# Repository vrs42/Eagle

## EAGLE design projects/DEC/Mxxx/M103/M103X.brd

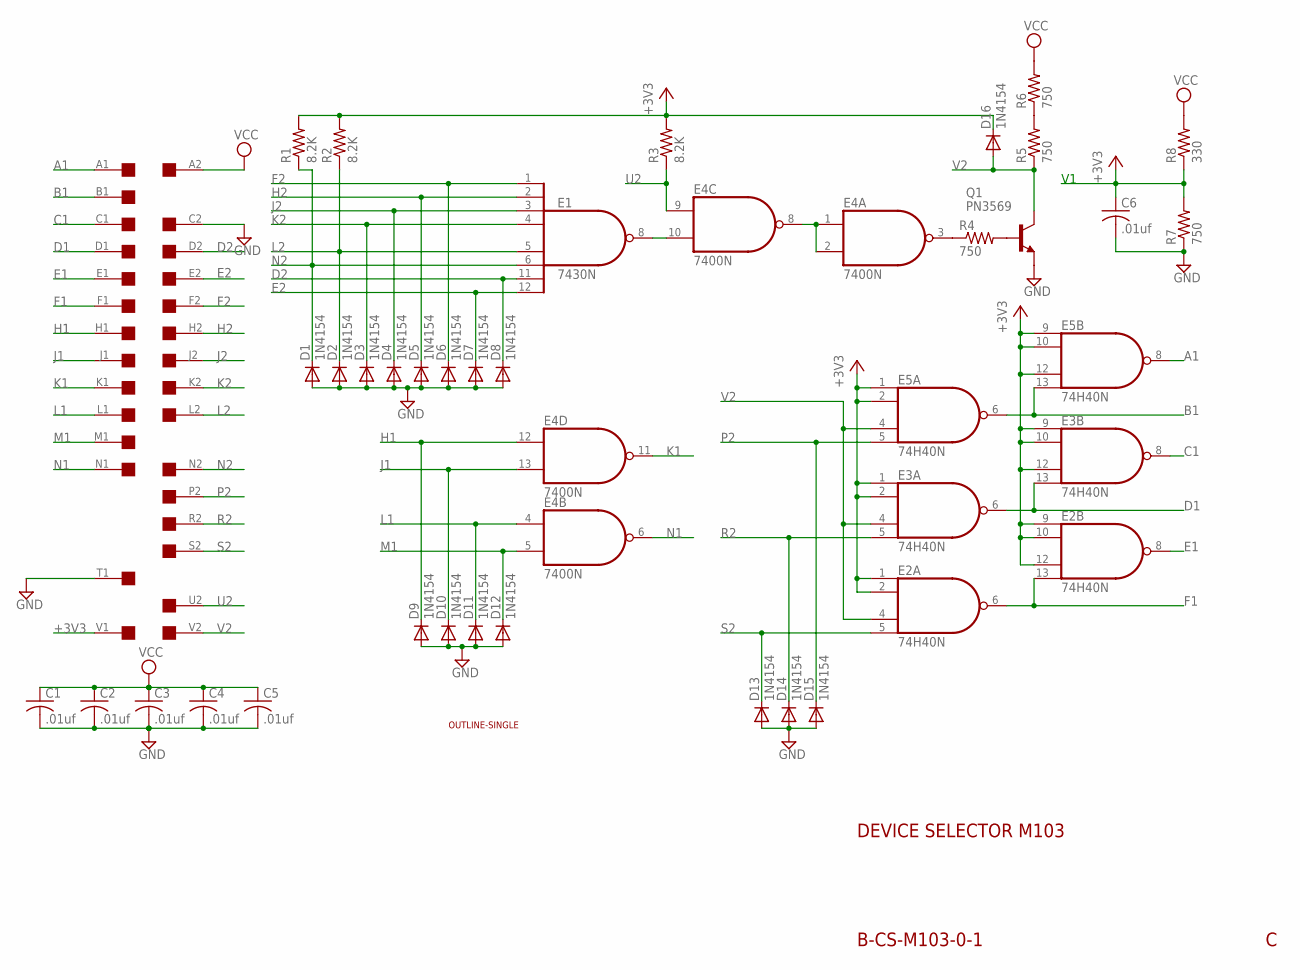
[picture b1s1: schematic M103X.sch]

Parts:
C1, C2, C3, C4, C5, C6: .01uf; C050-025X075
D1, D2, D3, D4, D5, D6, D7, D8, D9, D10, D11, D12, D13, D14, D15, D16: 1N4154; DO35-10
E1: 7430N; DIL14
E2, E3, E5: 74H40N; DIL14
E4: 7400N; DIL14
Q1: PN3569; TO39
R1, R2, R3: 8.2K; 0207/10
R4, R5, R6, R7: 750; 0207/10
R8: 330; 0207/10
U$8: SINGLE; EDGE-CON2
U$9: OUTLINE-SINGLE; SINGLE

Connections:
+3V3: C6.1, D16.C, E2.1 (I0), E2.2 (I1), E2.9 (I0), E2.10 (I1), E2.12 (I2), E3.1 (I0), E3.2 (I1), E3.9 (I0), E3.10 (I1), E3.12 (I2), E5.1 (I0), E5.2 (I1), E5.9 (I0), E5.10 (I1), E5.12 (I2), R1.2, R2.2, R3.2, R7.2, R8.1, U$8.V1
A1: E5.8 (O), U$8.A1
B1: E5.6 (O), E5.13 (I3), U$8.B1
C1: E3.8 (O), U$8.C1
D1: E3.6 (O), E3.13 (I3), U$8.D1
D2: D8.C, E1.11 (I6), U$8.D2
E1: E2.8 (O), U$8.E1
E2: D7.C, E1.12 (I7), U$8.E2
F1: E2.6 (O), E2.13 (I3), U$8.F1
F2: D6.C, E1.1 (I0), U$8.F2
GND: C1.2, C2.2, C3.2, C4.2, C5.2, C6.2, D1.A, D2.A, D3.A, D4.A, D5.A, D6.A, D7.A, D8.A, D9.A, D10.A, D11.A, D12.A, D13.A, D14.A, D15.A, E1.7 (GND), E2.7 (GND), E3.7 (GND), E4.7 (GND), E5.7 (GND), Q1.1 (E), R7.1, U$8.C2, U$8.T1
H1: D9.C, E4.12 (I0), U$8.H1
H2: D5.C, E1.2 (I1), U$8.H2
J1: D10.C, E4.13 (I1), U$8.J1
J2: D4.C, E1.3 (I2), U$8.J2
K1: E4.11 (O), U$8.K1
K2: D3.C, E1.4 (I3), U$8.K2
L1: D11.C, E4.4 (I0), U$8.L1
L2: D2.C, E1.5 (I4), R2.1, U$8.L2
M1: D12.C, E4.5 (I1), U$8.M1
N1: E4.6 (O), U$8.N1
N2: D1.C, E1.6 (I5), R1.1, U$8.N2
unnamed: E4.3 (O), R4.1
unnamed: Q1.2 (B), R4.2
unnamed: R5.2, R6.1
unnamed: E1.8 (O), E4.10 (I1)
unnamed: E4.1 (I0), E4.2 (I1), E4.8 (O)
P2: D15.C, E5.5 (I3), U$8.P2
R2: D14.C, E3.5 (I3), U$8.R2
S2: D13.C, E2.5 (I3), U$8.S2
U2: E4.9 (I0), R3.1, U$8.U2
V2: D16.A, E2.4 (I2), E3.4 (I2), E5.4 (I2), Q1.3 (C), R5.1, U$8.V2
VCC: C1.1, C2.1, C3.1, C4.1, C5.1, E1.14 (VCC), E2.14 (VCC), E3.14 (VCC), E4.14 (VCC), E5.14 (VCC), R6.2, R8.2, U$8.A2

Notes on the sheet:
DEVICE SELECTOR M103
B-CS-M103-0-1

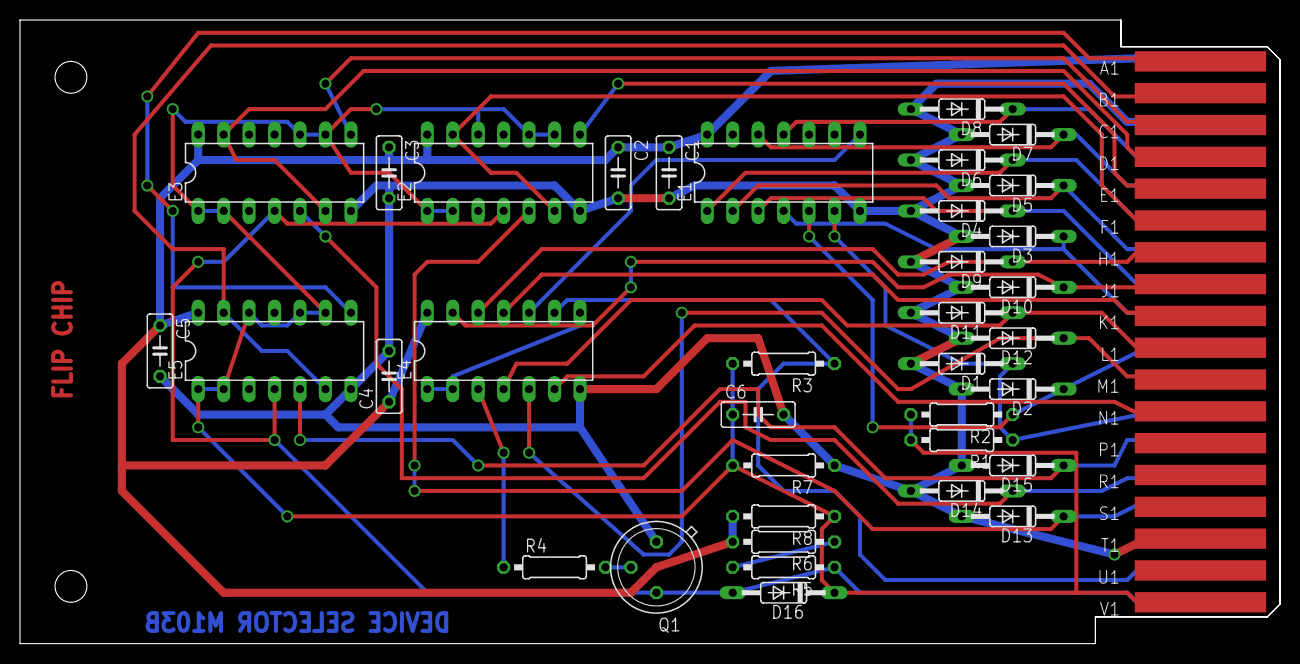
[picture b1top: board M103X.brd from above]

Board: 2 copper layers, 125.7 x 62.2 mm, 38 parts (0 on the bottom side), 33 nets.

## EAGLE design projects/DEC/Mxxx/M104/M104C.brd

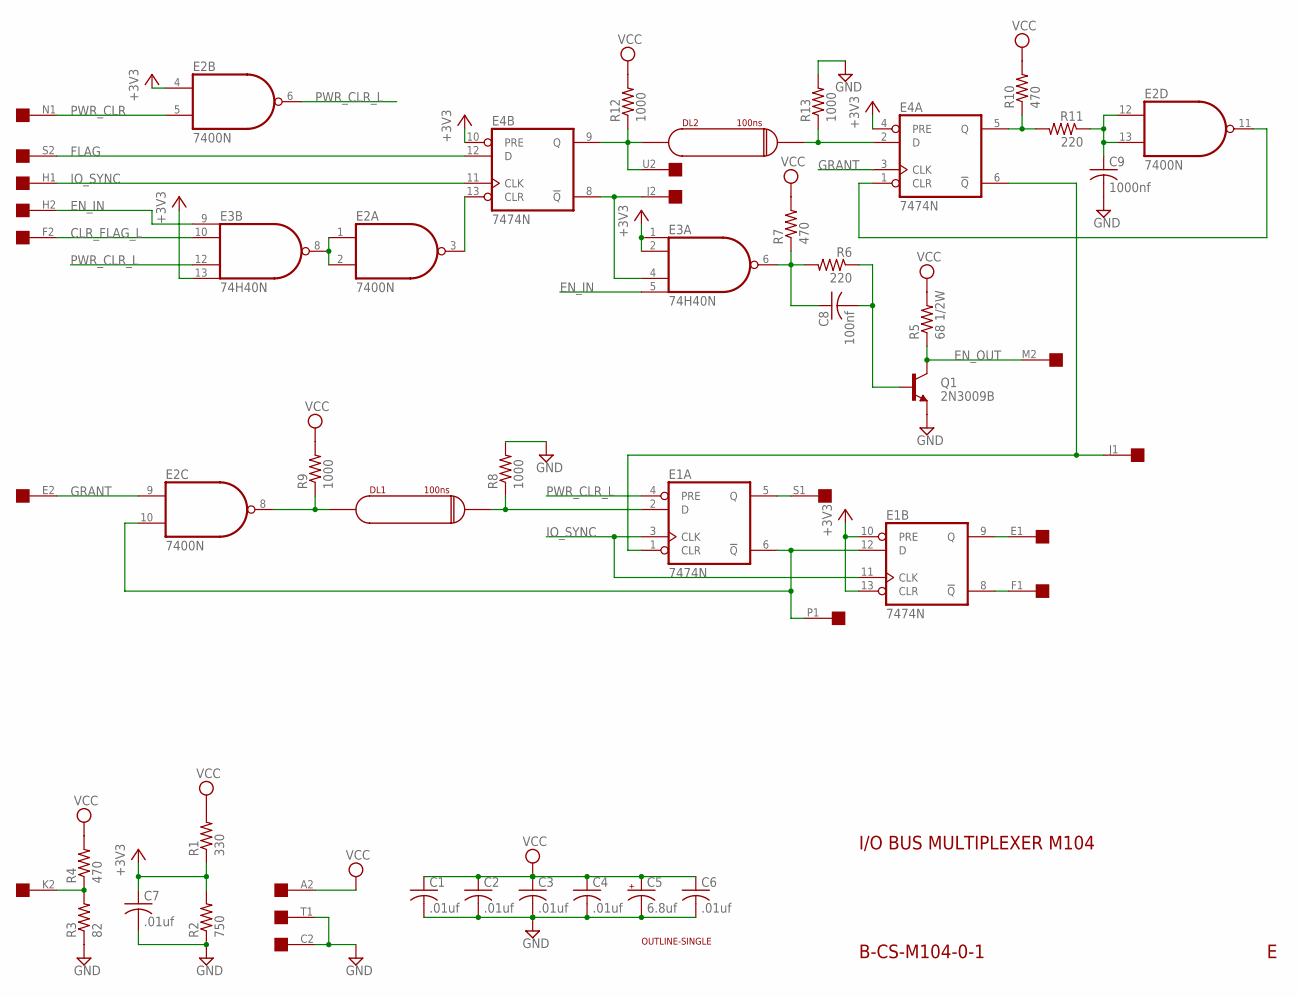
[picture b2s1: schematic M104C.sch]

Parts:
C1, C2, C3, C4, C6, C7: .01uf; C050-025X075
C5: 6.8uf; E15-5
C8: 100nf; C050-025X075
C9: 1000nf; C050-025X075
DL1, DL2: 100ns; RCL-L-XX-22
E1, E4: 7474N; DIL14
E2: 7400N; DIL14
E3: 74H40N; DIL14
Q1: 2N3009B; TO39
R1: 330; 0207/10
R2: 750; 0207/10
R3: 82; 0207/10
R4, R7, R10: 470; 0207/10
R5: 68 1/2W; 0411/15
R6, R11: 220; 0207/10
R8, R9, R12, R13: 1000; 0207/10
U$8: SINGLE; EDGE-CON2
U$9: OUTLINE-SINGLE; SINGLE

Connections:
+3V3: C7.1, E1.10 (PRE), E1.13 (CLR), E2.4 (I0), E3.1 (I0), E3.2 (I1), E3.13 (I3), E4.4 (PRE), E4.10 (PRE), R1.1, R2.2
CLR_FLAG_L: E3.10 (I1), U$8.F2
EN_IN: E3.5 (I3), E3.9 (I0), U$8.H2
EN_OUT: Q1.3 (C), R5.1, U$8.M2
FLAG: E4.12 (D), U$8.S2
GND: C1.2, C2.2, C3.2, C4.2, C5.-, C6.2, C7.2, C9.2, DL1.GND@1 (GND), DL1.GND@2 (GND), DL2.GND@1 (GND), DL2.GND@2 (GND), E1.7 (GND), E2.7 (GND), E3.7 (GND), E4.7 (GND), Q1.1 (E), R2.1, R3.1, R8.2, R13.2, U$8.C2, U$8.T1
GRANT: E2.9 (I0), E4.3 (CLK), U$8.E2
IO_SYNC: E1.3 (CLK), E1.11 (CLK), E4.11 (CLK), U$8.H1
K2: R3.2, R4.1, U$8.K2
unnamed: E1.1 (CLR), E4.6 (!Q), U$8.J1
unnamed: DL2.IN, E4.9 (Q), R12.1, U$8.U2
unnamed: E3.4 (I2), E4.8 (!Q), U$8.J2
unnamed: DL2.OUT, E4.2 (D), R13.1
unnamed: C8.1, E3.6 (O), R6.2, R7.1
unnamed: E2.1 (I0), E2.2 (I1), E3.8 (O)
unnamed: E2.3 (O), E4.13 (CLR)
unnamed: C9.1, E2.12 (I0), E2.13 (I1), R11.1
unnamed: E2.11 (O), E4.1 (CLR)
unnamed: DL1.IN, E2.8 (O), R9.1
unnamed: DL1.OUT, E1.2 (D), R8.1
unnamed: E1.6 (!Q), E1.12 (D), E2.10 (I1), U$8.P1
unnamed: E1.8 (!Q), U$8.F1
unnamed: E1.9 (Q), U$8.E1
unnamed: E1.5 (Q), U$8.S1
unnamed: E4.5 (Q), R10.1, R11.2
unnamed: C8.2, Q1.2 (B), R6.1
PWR_CLR: E2.5 (I1), U$8.N1
PWR_CLR_L: E1.4 (PRE), E2.6 (O), E3.12 (I2)
VCC: C1.1, C2.1, C3.1, C4.1, C5.+, C6.1, E1.14 (VCC), E2.14 (VCC), E3.14 (VCC), E4.14 (VCC), R1.2, R4.2, R5.2, R7.2, R9.2, R10.2, R12.2, U$8.A2

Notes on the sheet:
I/O BUS MULTIPLEXER M104
B-CS-M104-0-1

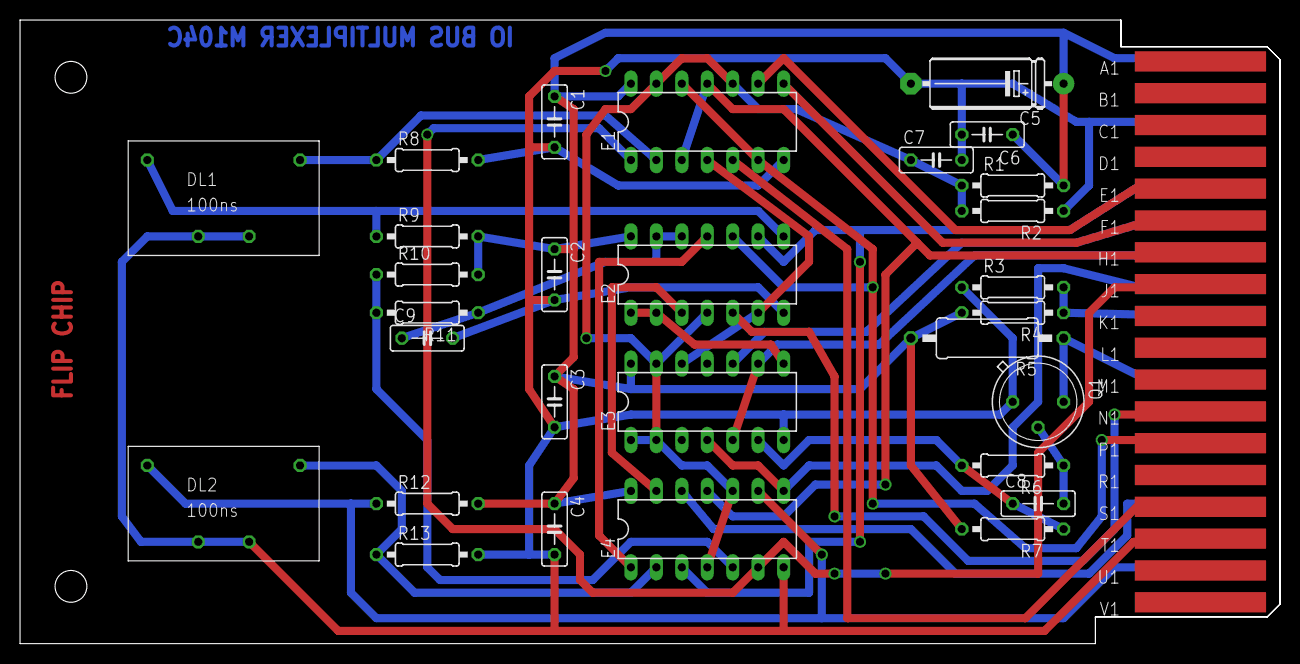
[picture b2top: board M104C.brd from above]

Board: 2 copper layers, 125.7 x 62.2 mm, 31 parts (0 on the bottom side), 29 nets.

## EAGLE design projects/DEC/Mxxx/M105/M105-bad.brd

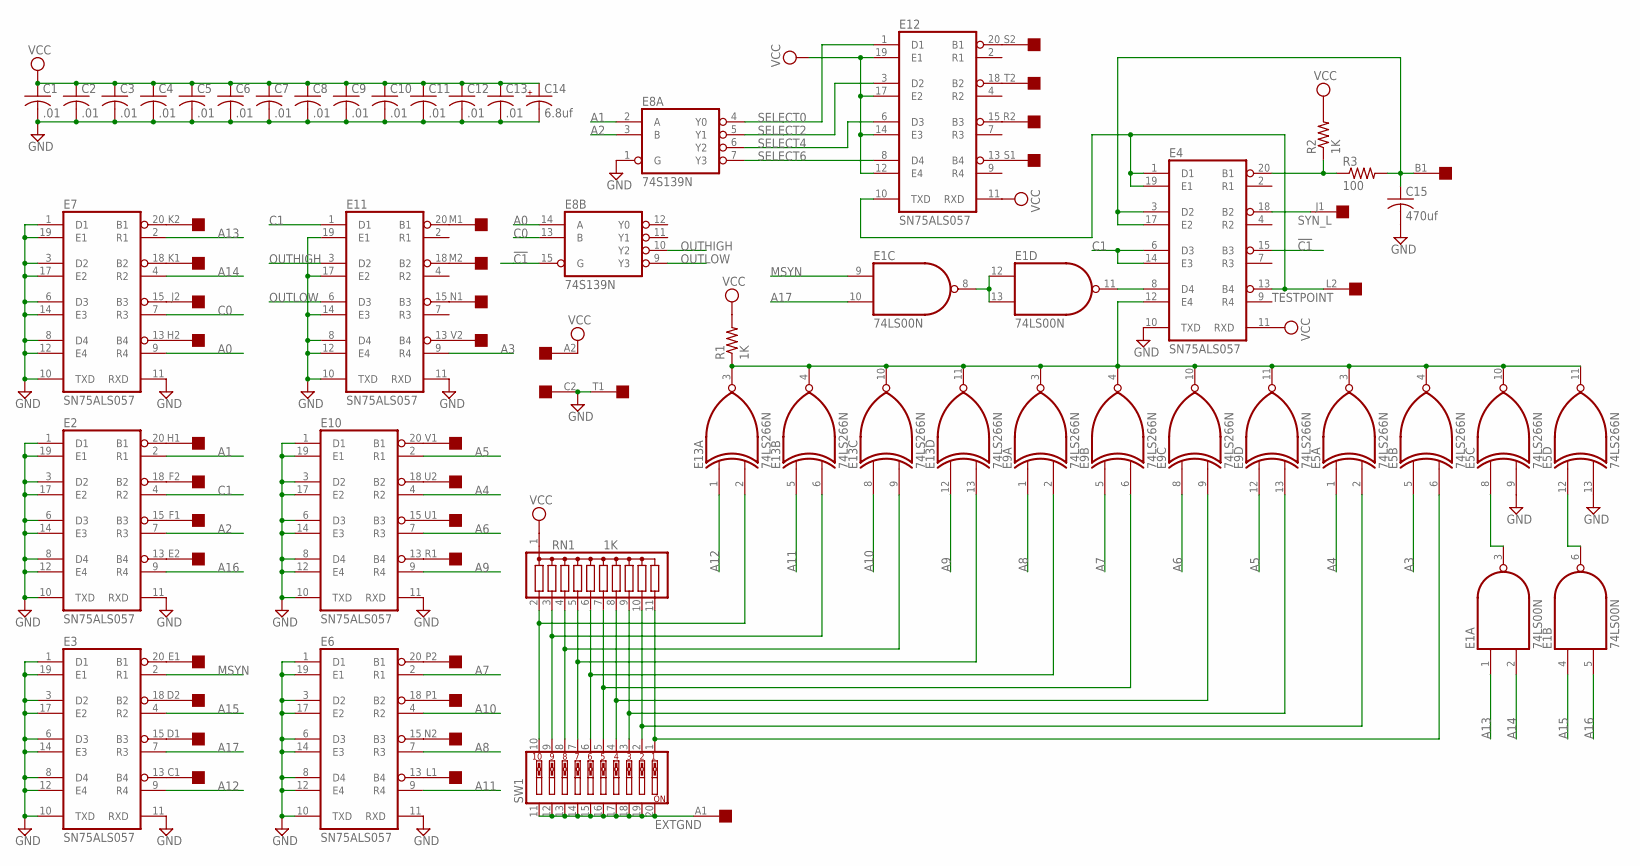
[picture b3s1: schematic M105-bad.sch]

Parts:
C1, C2, C3, C4, C5, C6, C7, C8, C9, C10, C11, C12, C13: .01; C050-025X075
C14: 6.8uf; E15-5
C15: 470uf; C050-025X075
E1: 74LS00N; DIL14
E2, E3, E4, E6, E7, E10, E11, E12: SN75ALS057; DIL20
E5, E9, E13: 74LS266N; DIL14
E8: 74S139N; DIL16
R1, R2: 1K; 0207/10
R3: 100; 0207/10
RN1: 1K; SIL11
SW1: SW_DIP-10; EDG-10
U$1: SINGLE; EDGE-CON2

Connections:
!C1: E4.15 (B3), E8.15 (G)
A0: E7.9 (R4), E8.14 (A)
A1: E2.2 (R1), E8.2 (A)
A2: E2.7 (R3), E8.3 (B)
A3: E5.5 (I0), E11.9 (R4)
A4: E5.1 (I0), E10.4 (R2)
A5: E9.12 (I0), E10.2 (R1)
A6: E9.8 (I0), E10.7 (R3)
A7: E6.2 (R1), E9.5 (I0)
A8: E6.7 (R3), E9.1 (I0)
A9: E10.9 (R4), E13.12 (I0)
A10: E6.4 (R2), E13.8 (I0)
A11: E6.9 (R4), E13.5 (I0)
A12: E3.9 (R4), E13.1 (I0)
A13: E1.1 (I0), E7.2 (R1)
A14: E1.2 (I1), E7.4 (R2)
A15: E1.4 (I0), E3.4 (R2)
A16: E1.5 (I1), E2.9 (R4)
A17: E1.10 (I1), E3.7 (R3)
C0: E7.7 (R3), E8.13 (B)
C1: E2.4 (R2), E4.6 (D3), E4.14 (E3), E11.1 (D1)
EXTGND: SW1.11, SW1.12, SW1.13, SW1.14, SW1.15, SW1.16, SW1.17, SW1.18, SW1.19, SW1.20, U$1.A1
GND: C1.2, C2.2, C3.2, C4.2, C5.2, C6.2, C7.2, C8.2, C9.2, C10.2, C11.2, C12.2, C13.2, C14.-, C15.2, E1.7 (GND), E2.1 (D1), E2.3 (D2), E2.6 (D3), E2.8 (D4), E2.10 (TXD), E2.11 (RXD), E2.12 (E4), E2.14 (E3), E2.16 (GND), E2.17 (E2), E2.19 (E1), E3.1 (D1), E3.3 (D2), E3.6 (D3), E3.8 (D4), E3.10 (TXD), E3.11 (RXD), E3.12 (E4), E3.14 (E3), E3.16 (GND), E3.17 (E2), E3.19 (E1), E4.10 (TXD), E4.16 (GND), E5.7 (GND), E5.9 (I1), E5.13 (I1), E6.1 (D1), E6.3 (D2), E6.6 (D3), E6.8 (D4), E6.10 (TXD), E6.11 (RXD), E6.12 (E4), E6.14 (E3), E6.16 (GND), E6.17 (E2), E6.19 (E1), E7.1 (D1), E7.3 (D2), E7.6 (D3), E7.8 (D4), E7.10 (TXD), E7.11 (RXD), E7.12 (E4), E7.14 (E3), E7.16 (GND), E7.17 (E2), E7.19 (E1), E8.1 (G), E8.8 (GND), E9.7 (GND), E10.1 (D1), E10.3 (D2), E10.6 (D3), E10.8 (D4), E10.10 (TXD), E10.11 (RXD), E10.12 (E4), E10.14 (E3), E10.16 (GND), E10.17 (E2), E10.19 (E1), E11.8 (D4), E11.10 (TXD), E11.11 (RXD), E11.12 (E4), E11.14 (E3), E11.16 (GND), E11.17 (E2), E11.19 (E1), E12.16 (GND), E13.7 (GND), U$1.C2, U$1.T1
MSYN: E1.9 (I0), E3.2 (R1)
unnamed: E3.18 (B2), U$1.D2
unnamed: E3.20 (B1), U$1.E1
unnamed: E3.15 (B3), U$1.D1
unnamed: E3.13 (B4), U$1.C1
unnamed: E2.18 (B2), U$1.F2
unnamed: E2.13 (B4), U$1.E2
unnamed: E2.20 (B1), U$1.H1
unnamed: E2.15 (B3), U$1.F1
unnamed: E7.20 (B1), U$1.K2
unnamed: E7.15 (B3), U$1.J2
unnamed: E7.13 (B4), U$1.H2
unnamed: E7.18 (B2), U$1.K1
unnamed: E6.15 (B3), U$1.N2
unnamed: E6.20 (B1), U$1.P2
unnamed: E6.13 (B4), U$1.L1
unnamed: E6.18 (B2), U$1.P1
unnamed: E10.18 (B2), U$1.U2
unnamed: E11.13 (B4), U$1.V2
unnamed: E10.13 (B4), U$1.R1
unnamed: E10.15 (B3), U$1.U1
unnamed: E10.20 (B1), U$1.V1
unnamed: E4.20 (B1), R2.1, R3.1
unnamed: E12.20 (B1), U$1.S2
unnamed: E12.18 (B2), U$1.T2
unnamed: E12.13 (B4), U$1.S1
unnamed: E12.15 (B3), U$1.R2
unnamed: E11.18 (B2), U$1.M2
unnamed: E11.15 (B3), U$1.N1
unnamed: E1.3 (O), E5.8 (I0)
unnamed: E1.6 (O), E5.12 (I0)
unnamed: E1.8 (O), E1.12 (I0), E1.13 (I1)
unnamed: E1.11 (O), E4.8 (D4)
unnamed: E5.6 (I1), RN1.11, SW1.1
unnamed: E5.2 (I1), RN1.10, SW1.2
unnamed: E9.13 (I1), RN1.9, SW1.3
unnamed: E9.9 (I1), RN1.8, SW1.4
unnamed: E9.6 (I1), RN1.7, SW1.5
unnamed: E9.2 (I1), RN1.6, SW1.6
unnamed: E13.13 (I1), RN1.5, SW1.7
unnamed: E13.9 (I1), RN1.4, SW1.8
unnamed: E13.6 (I1), RN1.3, SW1.9
unnamed: E13.2 (I1), RN1.2, SW1.10
unnamed: E4.12 (E4), E5.3 (O), E5.4 (O), E5.10 (O), E5.11 (O), E9.3 (O), E9.4 (O), E9.10 (O), E9.11 (O), E13.3 (O), E13.4 (O), E13.10 (O), E13.11 (O), R1.1
unnamed: C15.1, E4.3 (D2), E4.17 (E2), R3.2, U$1.B1
unnamed: E11.20 (B1), U$1.M1
OUTHIGH: E8.10 (Y2), E11.3 (D2)
OUTLOW: E8.9 (Y3), E11.6 (D3)
SELECT0: E8.4 (Y0), E12.1 (D1)
SELECT2: E8.5 (Y1), E12.3 (D2)
SELECT4: E8.6 (Y2), E12.6 (D3)
SELECT6: E8.7 (Y3), E12.8 (D4)
SYN_L: E4.18 (B2), U$1.J1
TESTPOINT: E4.1 (D1), E4.13 (B4), E4.19 (E1), E12.10 (TXD), U$1.L2
VCC: C1.1, C2.1, C3.1, C4.1, C5.1, C6.1, C7.1, C8.1, C9.1, C10.1, C11.1, C12.1, C13.1, C14.+, E1.14 (VCC), E2.5 (VCC), E3.5 (VCC), E4.5 (VCC), E4.11 (RXD), E5.14 (VCC), E6.5 (VCC), E7.5 (VCC), E8.16 (VCC), E9.14 (VCC), E10.5 (VCC), E11.5 (VCC), E12.5 (VCC), E12.11 (RXD), E12.12 (E4), E12.14 (E3), E12.17 (E2), E12.19 (E1), E13.14 (VCC), R1.2, R2.2, RN1.1, U$1.A2

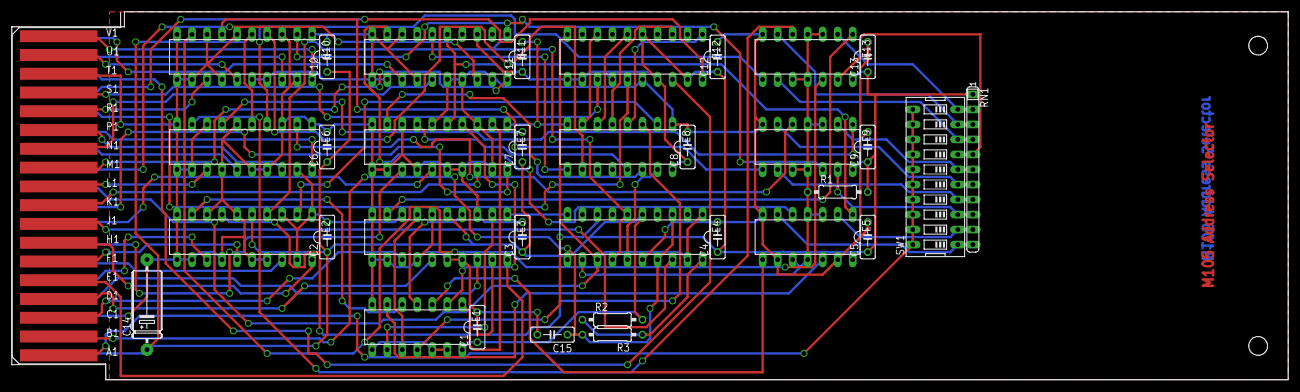
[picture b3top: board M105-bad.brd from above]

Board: 2 copper layers, 215.9 x 62.2 mm, 34 parts (0 on the bottom side), 78 nets.

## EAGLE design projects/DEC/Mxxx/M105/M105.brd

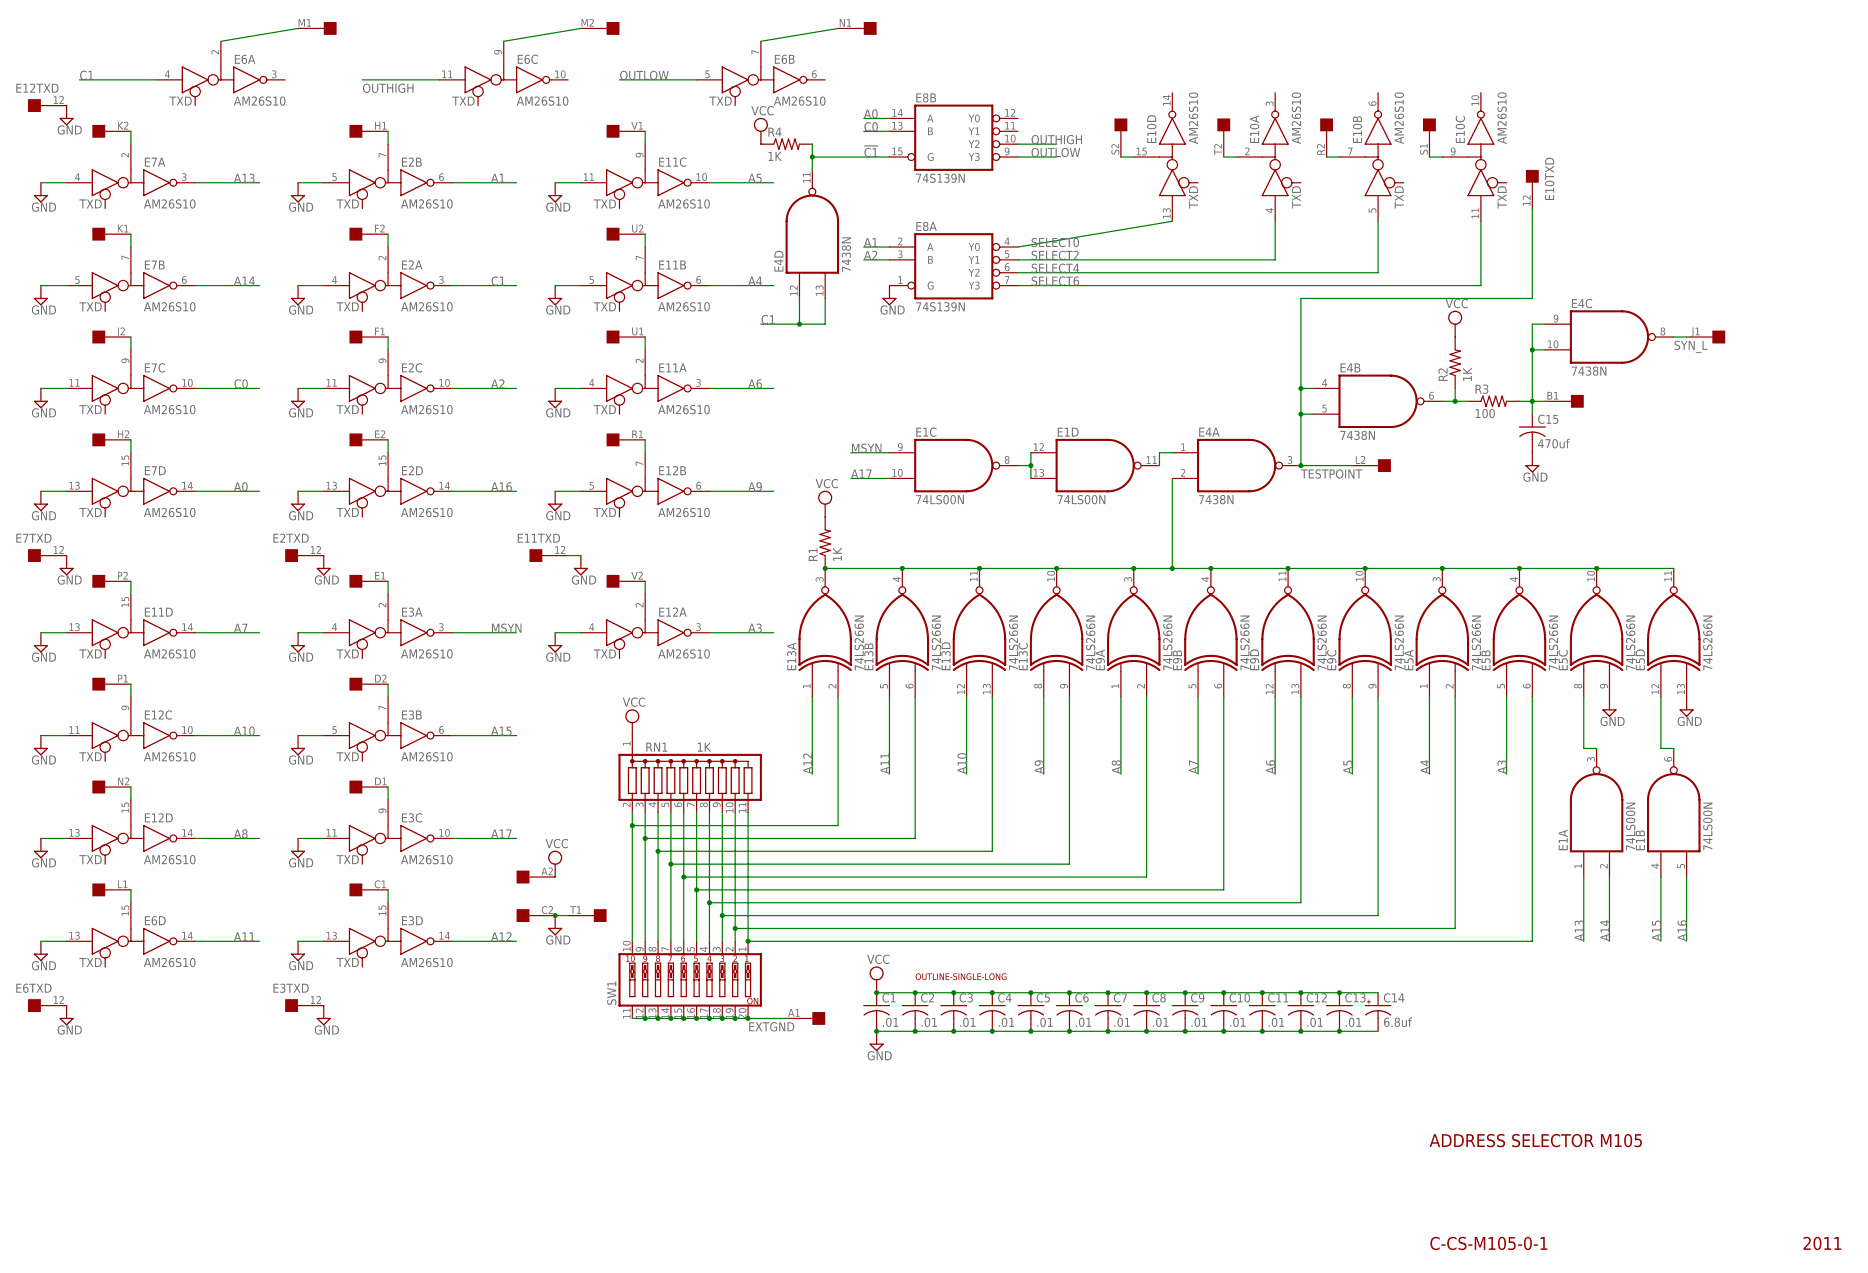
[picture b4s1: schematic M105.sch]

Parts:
C1, C2, C3, C4, C5, C6, C7, C8, C9, C10, C11, C12, C13: .01; C050-025X075
C14: 6.8uf; E15-5
C15: 470uf; C050-025X075
E1: 74LS00N; DIL14
E2, E3, E6, E7, E10, E11, E12: AM26S10; DIL16
E4: 7438N; DIL14
E5, E9, E13: 74LS266N; DIL14
E8: 74S139N; DIL16
R1, R2, R4: 1K; 0207/10
R3: 100; 0207/10
RN1: 1K; SIL11
SW1: SW_DIP-10; EDG-10
U$1: SINGLE; EDGE-CON2
U$2: OUTLINE-SINGLE-LONG; SINGLE-LONG

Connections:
!C1: E4.11 (O), E8.15 (G), R4.2
A0: E7.14 (R), E8.14 (A)
A1: E2.6 (R), E8.2 (A)
A2: E2.10 (R), E8.3 (B)
A3: E5.5 (I0), E12.3 (R)
A4: E5.1 (I0), E11.6 (R)
A5: E9.8 (I0), E11.10 (R)
A6: E9.12 (I0), E11.3 (R)
A7: E9.5 (I0), E11.14 (R)
A8: E9.1 (I0), E12.14 (R)
A9: E12.6 (R), E13.8 (I0)
A10: E12.10 (R), E13.12 (I0)
A11: E6.14 (R), E13.5 (I0)
A12: E3.14 (R), E13.1 (I0)
A13: E1.1 (I0), E7.3 (R)
A14: E1.2 (I1), E7.6 (R)
A15: E1.4 (I0), E3.6 (R)
A16: E1.5 (I1), E2.14 (R)
A17: E1.10 (I1), E3.10 (R)
C0: E7.10 (R), E8.13 (B)
C1: E2.3 (R), E4.12 (I0), E4.13 (I1), E6.4 (D)
EXTGND: SW1.11, SW1.12, SW1.13, SW1.14, SW1.15, SW1.16, SW1.17, SW1.18, SW1.19, SW1.20, U$1.A1
GND: C1.2, C2.2, C3.2, C4.2, C5.2, C6.2, C7.2, C8.2, C9.2, C10.2, C11.2, C12.2, C13.2, C14.-, C15.2, E1.7 (GND), E2.1 (GND), E2.4 (D), E2.5 (D), E2.8 (GND), E2.11 (D), E2.12 (TXD), E2.13 (D), E3.1 (GND), E3.4 (D), E3.5 (D), E3.8 (GND), E3.11 (D), E3.12 (TXD), E3.13 (D), E4.7 (GND), E5.7 (GND), E5.9 (I1), E5.13 (I1), E6.1 (GND), E6.8 (GND), E6.12 (TXD), E6.13 (D), E7.1 (GND), E7.4 (D), E7.5 (D), E7.8 (GND), E7.11 (D), E7.12 (TXD), E7.13 (D), E8.1 (G), E8.8 (GND), E9.7 (GND), E10.1 (GND), E10.8 (GND), E11.1 (GND), E11.4 (D), E11.5 (D), E11.8 (GND), E11.11 (D), E11.12 (TXD), E11.13 (D), E12.1 (GND), E12.4 (D), E12.5 (D), E12.8 (GND), E12.11 (D), E12.12 (TXD), E12.13 (D), E13.7 (GND), U$1.C2, U$1.T1
MSYN: E1.9 (I0), E3.3 (R)
unnamed: E3.2 (B), U$1.E1
unnamed: E3.7 (B), U$1.D2
unnamed: E3.9 (B), U$1.D1
unnamed: E3.15 (B), U$1.C1
unnamed: E2.7 (B), U$1.H1
unnamed: E2.2 (B), U$1.F2
unnamed: E2.9 (B), U$1.F1
unnamed: E2.15 (B), U$1.E2
unnamed: E7.2 (B), U$1.K2
unnamed: E7.7 (B), U$1.K1
unnamed: E7.9 (B), U$1.J2
unnamed: E7.15 (B), U$1.H2
unnamed: E11.15 (B), U$1.P2
unnamed: E12.9 (B), U$1.P1
unnamed: E12.15 (B), U$1.N2
unnamed: E6.15 (B), U$1.L1
unnamed: E12.7 (B), U$1.R1
unnamed: E12.2 (B), U$1.V2
unnamed: E11.2 (B), U$1.U1
unnamed: E11.7 (B), U$1.U2
unnamed: E11.9 (B), U$1.V1
unnamed: E4.6 (O), R2.1, R3.1
unnamed: E10.15 (B), U$1.S2
unnamed: E10.2 (B), U$1.T2
unnamed: E10.7 (B), U$1.R2
unnamed: E10.9 (B), U$1.S1
unnamed: E6.2 (B), U$1.M1
unnamed: E6.9 (B), U$1.M2
unnamed: E1.3 (O), E5.8 (I0)
unnamed: E1.6 (O), E5.12 (I0)
unnamed: E1.8 (O), E1.12 (I0), E1.13 (I1)
unnamed: E5.6 (I1), RN1.11, SW1.1
unnamed: E5.2 (I1), RN1.10, SW1.2
unnamed: E9.9 (I1), RN1.9, SW1.3
unnamed: E9.13 (I1), RN1.8, SW1.4
unnamed: E9.6 (I1), RN1.7, SW1.5
unnamed: E9.2 (I1), RN1.6, SW1.6
unnamed: E13.9 (I1), RN1.5, SW1.7
unnamed: E13.13 (I1), RN1.4, SW1.8
unnamed: E13.6 (I1), RN1.3, SW1.9
unnamed: E13.2 (I1), RN1.2, SW1.10
unnamed: E4.2 (I1), E5.3 (O), E5.4 (O), E5.10 (O), E5.11 (O), E9.3 (O), E9.4 (O), E9.10 (O), E9.11 (O), E13.3 (O), E13.4 (O), E13.10 (O), E13.11 (O), R1.1
unnamed: C15.1, E4.9 (I0), E4.10 (I1), R3.2, U$1.B1
unnamed: E6.7 (B), U$1.N1
unnamed: E1.11 (O), E4.1 (I0)
OUTHIGH: E6.11 (D), E8.10 (Y2)
OUTLOW: E6.5 (D), E8.9 (Y3)
SELECT0: E8.4 (Y0), E10.13 (D)
SELECT2: E8.5 (Y1), E10.4 (D)
SELECT4: E8.6 (Y2), E10.5 (D)
SELECT6: E8.7 (Y3), E10.11 (D)
SYN_L: E4.8 (O), U$1.J1
TESTPOINT: E4.3 (O), E4.4 (I0), E4.5 (I1), E10.12 (TXD), U$1.L2
VCC: C1.1, C2.1, C3.1, C4.1, C5.1, C6.1, C7.1, C8.1, C9.1, C10.1, C11.1, C12.1, C13.1, C14.+, E1.14 (VCC), E2.16 (VCC), E3.16 (VCC), E4.14 (VCC), E5.14 (VCC), E6.16 (VCC), E7.16 (VCC), E8.16 (VCC), E9.14 (VCC), E10.16 (VCC), E11.16 (VCC), E12.16 (VCC), E13.14 (VCC), R1.2, R2.2, R4.1, RN1.1, U$1.A2

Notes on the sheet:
ADDRESS SELECTOR M105
C-CS-M105-0-1
2011

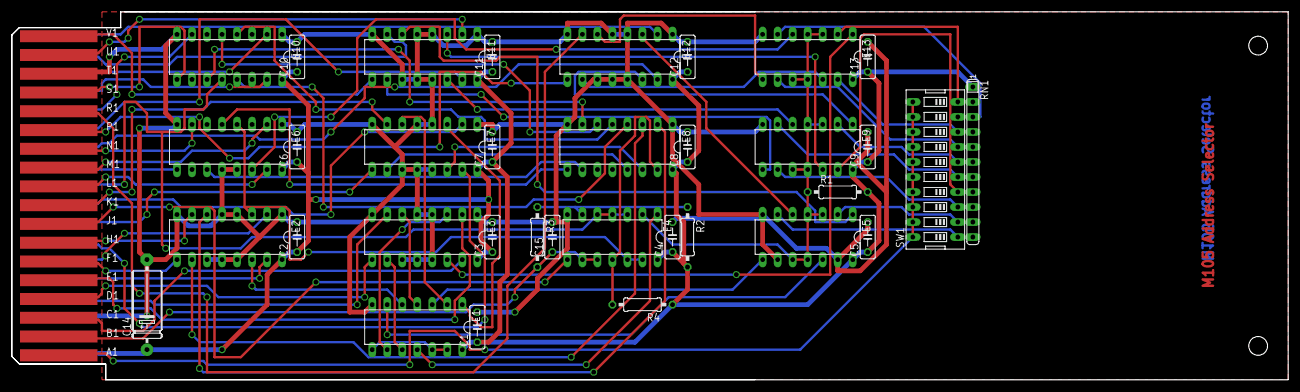
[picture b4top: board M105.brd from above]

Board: 2 copper layers, 215.9 x 62.2 mm, 36 parts (0 on the bottom side), 78 nets.

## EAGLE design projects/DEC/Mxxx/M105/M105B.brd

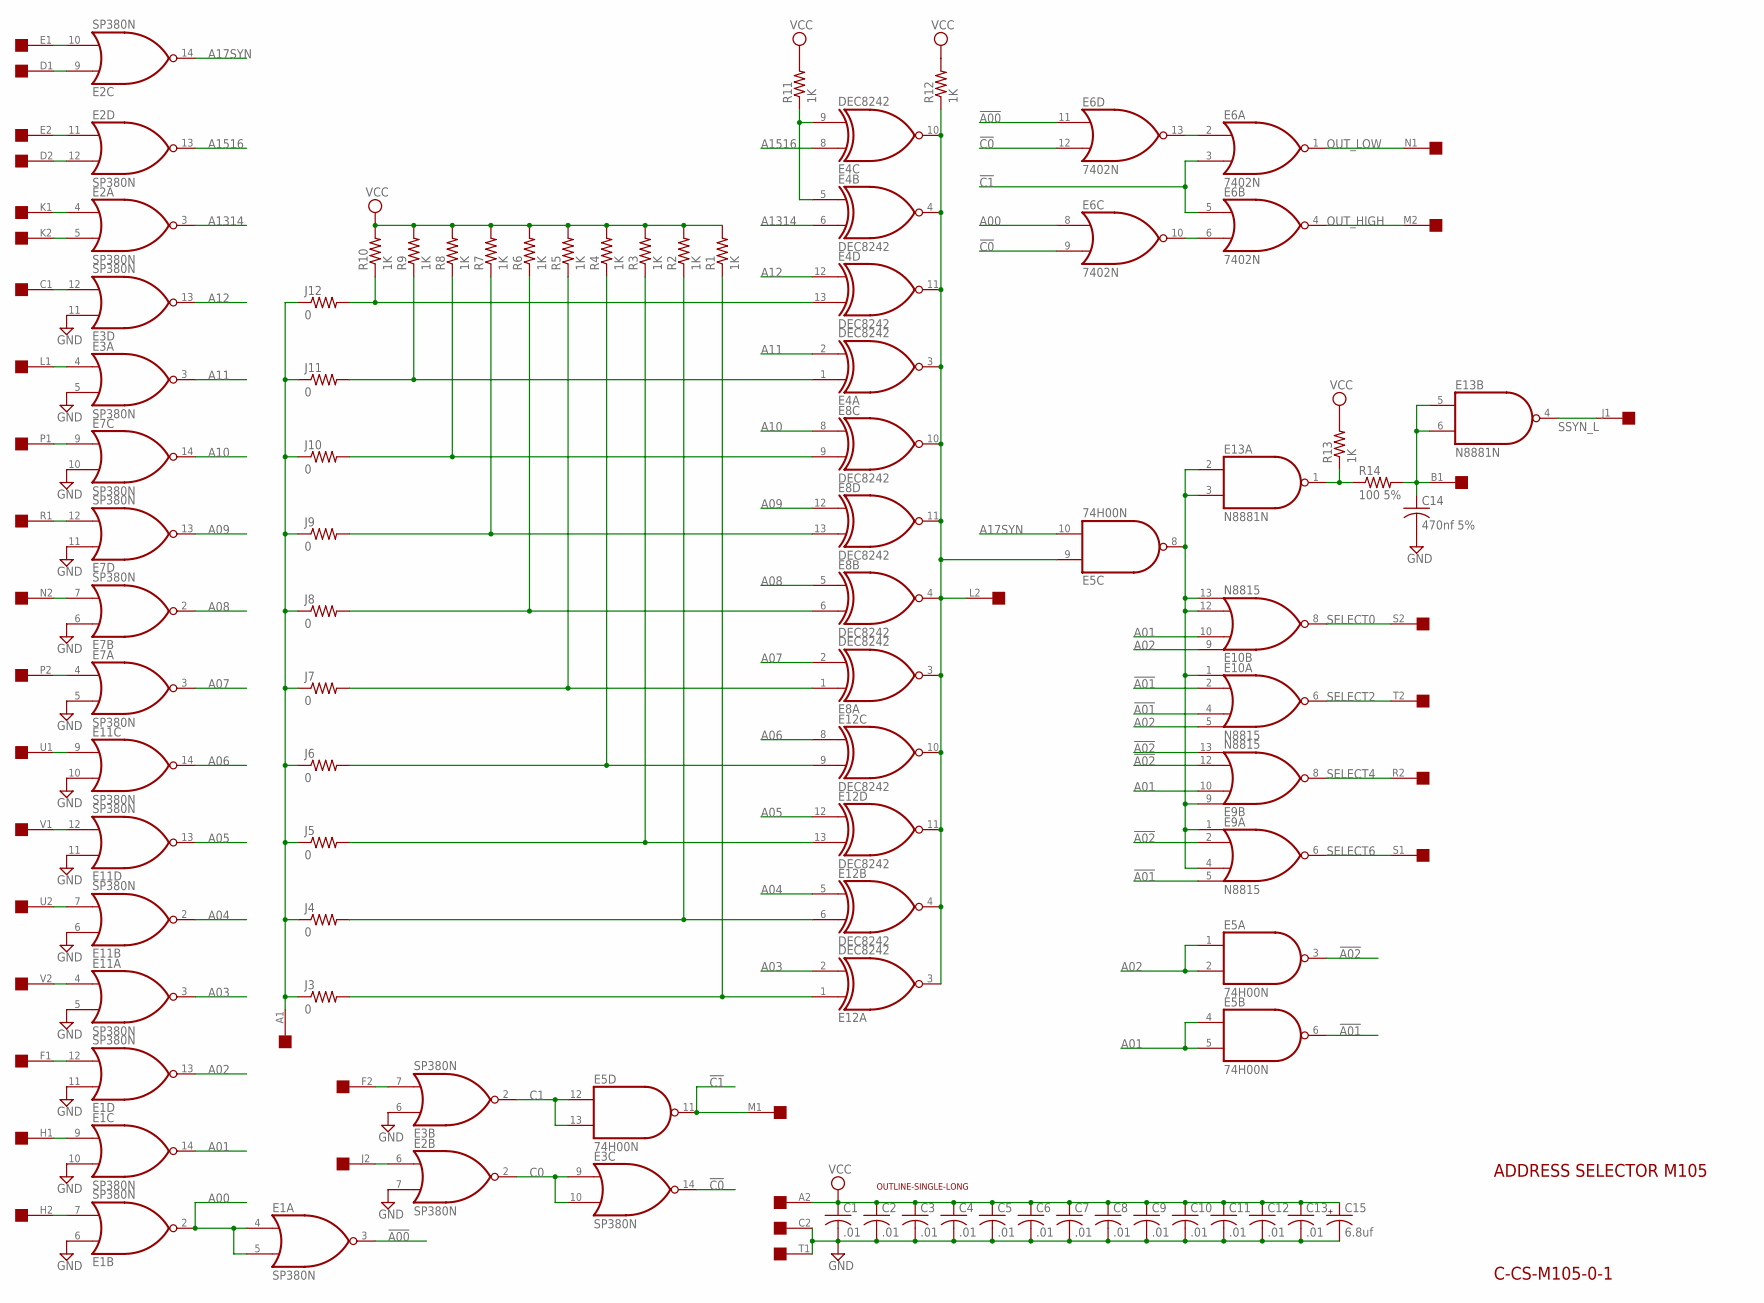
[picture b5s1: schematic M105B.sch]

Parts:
C1, C2, C3, C4, C5, C6, C7, C8, C9, C10, C11, C12, C13: .01; C050-025X075
C14: 470nf 5%; C050-025X075
C15: 6.8uf; E15-5
E1, E2, E3, E7, E11: SP380N; DIL14
E4, E8, E12: DEC8242; DIL14
E5: 74H00N; DIL14
E6: 7402N; DIL14
E9, E10: N8815; DIL14
E13: N8881N; DIL14
J3, J4, J5, J6, J7, J8, J9, J10, J11, J12: 0; 0207/10
R1, R2, R3, R4, R5, R6, R7, R8, R9, R10, R11, R12, R13: 1K; 0207/10
R14: 100 5%; 0207/10
U$1: SINGLE; EDGE-CON2
U$2: OUTLINE-SINGLE-LONG; SINGLE-LONG

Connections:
!A00: E1.3 (O), E6.11 (I0)
!A01: E5.6 (O), E9.5 (I3), E10.2 (I1), E10.4 (I2)
!A02: E5.3 (O), E9.2 (I1), E9.12 (I2), E9.13 (I3)
!C0: E3.14 (O), E6.9 (I1), E6.12 (I1)
!C1: E5.11 (O), E6.3 (I1), E6.5 (I0), U$1.M1
A00: E1.2 (O), E1.4 (I0), E1.5 (I1), E6.8 (I0)
A01: E1.14 (O), E5.4 (I0), E5.5 (I1), E9.10 (I1), E10.10 (I1)
A02: E1.13 (O), E5.1 (I0), E5.2 (I1), E10.5 (I3), E10.9 (I0)
A03: E11.3 (O), E12.2 (I1)
A04: E11.2 (O), E12.5 (I0)
A05: E11.13 (O), E12.12 (I0)
A06: E11.14 (O), E12.8 (I0)
A07: E7.3 (O), E8.2 (I1)
A08: E7.2 (O), E8.5 (I0)
A09: E7.13 (O), E8.12 (I0)
A10: E7.14 (O), E8.8 (I0)
A11: E3.3 (O), E4.2 (I1)
A12: E3.13 (O), E4.12 (I0)
A17SYN: E2.14 (O), E5.10 (I1)
A1314: E2.3 (O), E4.6 (I1)
A1516: E2.13 (O), E4.8 (I0)
C0: E2.2 (O), E3.9 (I0), E3.10 (I1)
C1: E3.2 (O), E5.12 (I0), E5.13 (I1)
GND: C1.2, C2.2, C3.2, C4.2, C5.2, C6.2, C7.2, C8.2, C9.2, C10.2, C11.2, C12.2, C13.2, C14.2, C15.-, E1.1 (GND), E1.6 (I0), E1.10 (I1), E1.11 (I0), E2.1 (GND), E2.7 (I1), E3.1 (GND), E3.5 (I1), E3.6 (I0), E3.11 (I0), E4.7 (GND), E5.7 (GND), E6.7 (GND), E7.1 (GND), E7.5 (I1), E7.6 (I0), E7.10 (I1), E7.11 (I0), E8.7 (GND), E9.7 (GND), E10.7 (GND), E11.1 (GND), E11.5 (I1), E11.6 (I0), E11.10 (I1), E11.11 (I0), E12.7 (GND), E13.7 (GND), U$1.C2, U$1.T1
unnamed: E2.10 (I1), U$1.E1
unnamed: E2.9 (I0), U$1.D1
unnamed: E2.11 (I0), U$1.E2
unnamed: E2.12 (I1), U$1.D2
unnamed: E2.4 (I0), U$1.K1
unnamed: E2.5 (I1), U$1.K2
unnamed: E3.12 (I1), U$1.C1
unnamed: E3.4 (I0), U$1.L1
unnamed: E7.9 (I0), U$1.P1
unnamed: E7.7 (I1), U$1.N2
unnamed: E7.12 (I1), U$1.R1
unnamed: E7.4 (I0), U$1.P2
unnamed: E11.9 (I0), U$1.U1
unnamed: E11.12 (I1), U$1.V1
unnamed: E11.7 (I1), U$1.U2
unnamed: E11.4 (I0), U$1.V2
unnamed: E1.12 (I1), U$1.F1
unnamed: E1.7 (I1), U$1.H2
unnamed: E1.9 (I0), U$1.H1
unnamed: J3.1, J4.1, J5.1, J6.1, J7.1, J8.1, J9.1, J10.1, J11.1, J12.1, U$1.A1
unnamed: E4.13 (I1), J12.2, R10.1
unnamed: E13.1 (O), R13.1, R14.1
unnamed: E2.6 (I0), U$1.J2
unnamed: E3.7 (I1), U$1.F2
unnamed: E5.8 (O), E9.1 (I0), E9.4 (I2), E9.9 (I0), E10.1 (I0), E10.12 (I2), E10.13 (I3), E13.2 (I0), E13.3 (I1)
unnamed: E4.1 (I0), J11.2, R9.1
unnamed: E4.5 (I0), E4.9 (I1), R11.1
unnamed: E12.1 (I0), J3.2, R1.1
unnamed: E12.6 (I1), J4.2, R2.1
unnamed: E12.13 (I1), J5.2, R3.1
unnamed: E12.9 (I1), J6.2, R4.1
unnamed: E8.6 (I1), J8.2, R6.1
unnamed: E6.2 (I0), E6.13 (O)
unnamed: E8.13 (I1), J9.2, R7.1
unnamed: E8.9 (I1), J10.2, R8.1
unnamed: E6.6 (I1), E6.10 (O)
unnamed: E4.3 (O), E4.4 (O), E4.10 (O), E4.11 (O), E5.9 (I0), E8.3 (O), E8.4 (O), E8.10 (O), E8.11 (O), E12.3 (O), E12.4 (O), E12.10 (O), E12.11 (O), R12.1, U$1.L2
unnamed: C14.1, E13.5 (I0), E13.6 (I1), R14.2, U$1.B1
unnamed: E8.1 (I0), J7.2, R5.1
OUT_HIGH: E6.4 (O), U$1.M2
OUT_LOW: E6.1 (O), U$1.N1
SELECT0: E10.8 (O), U$1.S2
SELECT2: E10.6 (O), U$1.T2
SELECT4: E9.8 (O), U$1.R2
SELECT6: E9.6 (O), U$1.S1
SSYN_L: E13.4 (O), U$1.J1
VCC: C1.1, C2.1, C3.1, C4.1, C5.1, C6.1, C7.1, C8.1, C9.1, C10.1, C11.1, C12.1, C13.1, C15.+, E1.8 (VCC), E2.8 (VCC), E3.8 (VCC), E4.14 (VCC), E5.14 (VCC), E6.14 (VCC), E7.8 (VCC), E8.14 (VCC), E9.14 (VCC), E10.14 (VCC), E11.8 (VCC), E12.14 (VCC), E13.14 (VCC), R1.2, R2.2, R3.2, R4.2, R5.2, R6.2, R7.2, R8.2, R9.2, R10.2, R11.2, R12.2, R13.2, U$1.A2

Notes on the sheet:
ADDRESS SELECTOR M105
C-CS-M105-0-1

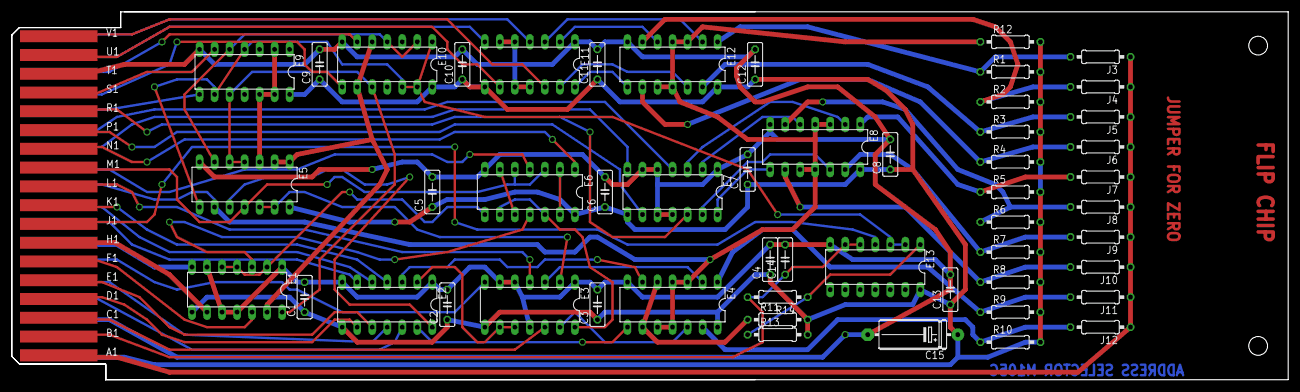
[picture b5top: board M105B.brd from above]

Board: 2 copper layers, 215.9 x 62.2 mm, 54 parts (0 on the bottom side), 71 nets.
